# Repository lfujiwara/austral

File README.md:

# Austral

[Conheça a Austral](https://lfujiwara.github.io/austral/)

A Austral é uma plataforma de IoT AI-native para a cadeia de frio. Combina temperatura e consumo de energia de freezers e refrigeradores para ajudar mercados, bares e restaurantes a reduzir perdas de produtos e gastos com energia.

O dono recebe avisos pelo WhatsApp com a causa provável do problema e o valor do estoque em risco. Na mesma conversa, pode consultar o equipamento e chamar uma empresa de manutenção.

O técnico recebe um laudo com gráficos, modelo do equipamento e histórico de reparos. Empresas parceiras acompanham os chamados pelo webapp ou integram seus sistemas pelas APIs da Austral.

Projeto para a trilha Logística & automação do Hack Brasil 2026.

O firmware do dispositivo e o ambiente de desenvolvimento ficam em [`device/`](device/README.md).

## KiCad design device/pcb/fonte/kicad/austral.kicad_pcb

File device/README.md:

# Dispositivo

Firmware do dispositivo Austral e um ambiente de desenvolvimento virtual. O ambiente roda o firmware num ESP32 emulado, com sensores e Wi-Fi simulados, e mostra as leituras num gráfico. Não precisa de placa nem de sensores.

Esta branch é a variante offline. A buzina e a tela ficam fora do firmware que a placa roda. As seções "Buzina" e "Tela" explicam como religar.

## O que tem aqui

- `firmware/device.yaml`: firmware em ESPHome para ESP32.
- `firmware/packages/buzzer.yaml`: buzina no GPIO25 e as ações que a ligam no alarme local. A variante offline inclui `packages/buzzer_off.yaml` no lugar dele.
- `firmware/packages/buzzer_off.yaml`: pacote vazio incluído no lugar da buzina.
- `firmware/packages/display.yaml`: tela OLED. A variante offline inclui `packages/display_off.yaml` no lugar dele.
- `firmware/packages/display_off.yaml`: pacote vazio incluído no lugar da tela.
- `schema/mqtt.json`: formato de cada tópico MQTT que o dispositivo publica ou aceita.
- `emulator/`: script que compila o QEMU com Wi-Fi para ESP32 e os patches deste repositório.
- `server/`: servidor local. É o broker MQTT com TLS, serve a página com o gráfico e grava o histórico das leituras em `.local/data/`.
- `scenarios/`: roteiros que mudam a temperatura e o Wi-Fi ao longo do tempo.
- `test/e2e.mjs`: teste de ponta a ponta no emulador.
- `dev`: comando que reúne tudo. `./dev lan` prepara o broker TLS na rede de casa.

## Firmware

O firmware lê um DS18B20 no barramento 1-Wire do GPIO4, a sonda de ar. Ele pega o primeiro dispositivo que a busca ROM encontra no setup (`index: 0`), sem endereço gravado. Lê a cada 10 segundos, com resolução de 12 bits. O intervalo vai de 1 a 300 segundos e fica salvo na flash.

## Sensores e ligação

O DS18B20 da sonda de ar fica no barramento 1-Wire do GPIO4.

O HC-SR04 mede a distância até a porta. O Trig fica no GPIO26 e o Echo no GPIO27, atrás de um divisor de 1 kΩ e 2 kΩ. O sensor mede a cada 100 ms. O dispositivo publica a cada 500 ms a mediana das últimas 10 leituras, em metros. Sem eco, o valor é `nan`. "Door open" continua saindo dessa distância, depois da calibração.

O contato de porta é um reed switch MC-38, normalmente aberto, sem polaridade. Um fio vai no GPIO33 e o outro no GND. O ímã fica na porta. O pino usa o pull-up interno. Com o ímã perto, o contato fecha, o pino vai a nível baixo e a porta conta como fechada (`OFF`). Com o contato aberto, o pino fica em nível alto e a porta conta como aberta (`ON`). O estado sai em `binary_sensor/door_contact/state`, com um filtro de 100 ms. O emulador não simula esse pino: lá o valor não acompanha uma porta de verdade.

Para calibrar a distância, feche a porta e aperte "Calibrate door" na página web do dispositivo, ou publique `PRESS` em `button/calibrate_door/command`. O dispositivo mede por 3 segundos, calcula a mediana das leituras válidas e grava "Door closed distance". Com menos de 5 leituras válidas, mantém o valor antigo e registra um aviso no log. Esse valor também aceita ajuste manual e fica salvo na flash. O valor 0 significa sem calibração.

"Door open" fica `ON` quando a distância passa de "Door closed distance" mais 0,05 m por 2 segundos. Um eco ausente conta como porta aberta. Volta a `OFF` depois de 1 segundo. O estado da porta só é publicado depois da calibração. A margem é a substituição `door_margin` em `firmware/device.yaml`.

As leituras saem por MQTT com TLS na porta 8883. A seção "Formato dos dados" descreve os tópicos.

O alarme local observa a sonda de ar. O limite padrão é 5,0 °C. A entidade "Alarm threshold" guarda esse limite na flash. Dá para mudar pela página web do dispositivo ou por `number/alarm_threshold/command`, de -40 a 40 °C, em passos de 0,1. O alarme publica `ON` quando o ar fica acima do limite por 10 minutos e `OFF` 1 minuto depois de voltar ao limite ou abaixo. Funciona sem Wi-Fi e sem MQTT. Nesta variante o alarme local só publica o estado.

Nesta variante a tela não entra no firmware. O endereço do broker pode mudar pelo servidor web do dispositivo ou por MQTT. O novo endereço fica salvo na flash.

Para gravar numa placa real na rede de casa, siga a seção "Rede de casa no Mac". O código ROM da sonda aparece no log do primeiro boot.

## Buzina

O código da buzina continua no repositório, em `firmware/packages/buzzer.yaml`. Ele define a saída no GPIO25, a chave "Buzzer" e as ações que ligam e desligam essa chave quando o alarme local muda.

`firmware/device.yaml` escolhe o pacote pela substituição `buzzer_package`. A variante offline aponta para `packages/buzzer_off.yaml`. Esse pacote entra vazio: o GPIO25 fica livre e o alarme local fica só no MQTT.

Para reativar a buzina, troque a substituição e grave o firmware de novo:

```yaml
buzzer_package: packages/buzzer.yaml
```

A chave volta a publicar `switch/buzzer/state` (`ON` ou `OFF`) e a aceitar `switch/buzzer/command` (`ON`, `OFF` ou `TOGGLE`). Inclua esses dois tópicos de novo em `schema/mqtt.json` para o servidor e o `./dev test` aceitarem as mensagens. O teste também recusa qualquer tópico com `buzzer` no nome. Tire essa checagem ao religar a buzina.

## Tela

O código da tela continua no repositório, em `firmware/packages/display.yaml`. Ele liga o OLED SSD1306 de 128x32 no I2C, SDA no GPIO21 e SCL no GPIO22, endereço 0x3C. A tela alterna duas páginas a cada 6 segundos: o gráfico do ar nos últimos 30 minutos, com o valor atual e o limite ao lado, e a página com porta, alarme, Wi-Fi e MQTT.

`firmware/device.yaml` escolhe o pacote pela substituição `display_package`. Esta branch aponta para `packages/display_off.yaml`. Esse pacote entra vazio. O I2C não sobe e a tela não é inicializada.

Para religar a tela, troque a substituição e grave o firmware de novo:

```yaml
display_package: packages/display.yaml
```

## Formato dos dados

O arquivo `schema/mqtt.json` é a referência. Ele lista cada tópico com o padrão do payload, a unidade e a frequência. O servidor confere cada mensagem com esse arquivo. O teste falha se chegar um tópico fora dele ou um payload fora do padrão.

Os tópicos do dispositivo começam com `austral/<dispositivo>/`. O payload é texto puro, sem JSON. Essas mensagens saem com QoS 0 e `retain`. Quem assina recebe na hora o último valor de cada tópico.

| Tópico | Payload | Unidade | Frequência |
| --- | --- | --- | --- |
| `status` | `online` ou `offline` | | na conexão e na queda |
| `sensor/air_temperature/state` | número com uma casa, ou `nan` | °C | 10 s |
| `sensor/door_distance/state` | número com três casas, ou `nan` | m | 0,5 s |
| `sensor/wifi_signal/state` | inteiro | dBm | 60 s |
| `sensor/uptime/state` | inteiro | s | 60 s |
| `binary_sensor/door_contact/state` | `ON` ou `OFF` | | quando muda |
| `binary_sensor/door_open/state` | `ON` ou `OFF` | | quando muda, depois da calibração |
| `binary_sensor/local_temperature_alarm/state` | `ON` ou `OFF` | | quando muda |
| `text/mqtt_broker/state` | endereço do broker | | quando muda |
| `number/read_interval/state` | número | s | quando muda |
| `number/door_closed_distance/state` | número | m | quando muda |
| `number/alarm_threshold/state` | número | °C | quando muda |
| `debug` | linha de log do dispositivo | | a cada log |

Quando o checksum da sonda falha, o log `debug` traz um aviso `Scratch pad: 50.05.4B.46.7F.FF.0C.10.1C (1C)`. São os 9 bytes que a sonda enviou e, entre parênteses, o CRC que o firmware calculou com os 8 primeiros. O painel mostra essas linhas na seção Debug da sonda. O firmware usa uma cópia local do componente `dallas_temp` do ESPHome 2026.6.5 em `firmware/components/dallas_temp`. Ela difere do original em duas linhas: o nível do log do scratch pad inválido passa de DEBUG para WARN, e o setup registra o endereço encontrado pela busca (ou que nenhum dispositivo apareceu).

`nan` indica um sensor que não respondeu. O broker publica `offline` em nome do dispositivo quando perde a conexão com ele. `binary_sensor/door_open/state` só aparece depois da calibração.

O ESPHome também publica `esphome/discover/<dispositivo>` a cada conexão, com `retain`. O payload é um JSON com os endereços IP, o MAC, a versão do ESPHome e a placa. Esse tópico fica fora do prefixo e o servidor não confere o formato dele.

O dispositivo aceita cinco comandos: `text/mqtt_broker/command` (novo endereço), `number/read_interval/command` (segundos), `number/door_closed_distance/command` (metros), `number/alarm_threshold/command` (°C, de -40 a 40) e `button/calibrate_door/command` (`PRESS`).

A página do servidor mostra o último payload bruto de cada tópico e se ele bate com o schema.

## Histórico das leituras

O servidor grava cada leitura numérica num arquivo neste Mac, em `.local/data/readings-YYYY-MM-DD.jsonl`. A data do arquivo segue o fuso America/Sao_Paulo. A pasta `.local/` fica fora do git. Entram todos os sensores numéricos, por exemplo a temperatura do ar, a distância da porta, o sinal do Wi-Fi e o tempo ligado. Cada linha é um JSON:

```json
{"t":"2026-11-28T04:30:00.123-03:00","ms":1764315000123,"device":"austral-device","sensor":"air_temperature","value":22.8}
```

`t` é o instante com o fuso de Brasília. `value` é o número, ou `null` quando o sensor não respondeu (`nan`). O arquivo acumula o dia inteiro, sem o limite do gráfico. O painel continua usando um buffer em memória das últimas 4.320 leituras de cada sensor. Ao subir, o servidor recarrega do arquivo do dia as últimas 4.320 de cada um, para o gráfico não nascer vazio.

## Rede de casa no Mac

A placa manda as leituras para o broker MQTT deste repositório, com TLS e senha. O modo normal continua só em `127.0.0.1`. A rede de casa entra com `--lan` ou com `AUSTRAL_LAN=1`. Nesse modo a porta 8883 abre na rede, só com TLS. O gráfico fica em `http://127.0.0.1:8080`, neste Mac. Nenhuma porta sem TLS fica na rede.

A placa precisa do Wi-Fi de 2,4 GHz, o mesmo do Mac. Se o Mac estiver em `192.168.0.x`, o comando usa esse endereço. Se o IP mudar, rode `./dev lan prepare` de novo e grave o firmware outra vez. Rodar de novo mantém o mesmo usuário e a mesma senha.

Requisitos: Node 20.11 ou mais novo, Python 3 e `openssl`. O `openssl` já vem no macOS. Não precisa de Docker.

```sh
cd device
./dev lan prepare
```

O comando grava em `firmware/secrets.yaml`, sem mostrar senha:

- `mqtt_broker`: o IP da rede, por exemplo `192.168.0.23`. Use esse IP. O certificado também traz o nome `<hostname>.local`. Só troque `mqtt_broker` por esse nome se quiser que a placa disque o nome em vez do IP.
- `mqtt_username` e `mqtt_password`: gerados em `.local/credentials.env`.
- `mqtt_ca`: o conteúdo de `.local/tls/ca.pem`, a autoridade que assina o broker. O comando cola esse texto no secrets. Não use o certificado do servidor no lugar da autoridade.

`wifi_ssid` e `wifi_password` não são alterados. Se ainda estiverem de exemplo, preencha os dois no mesmo arquivo. Não copie o arquivo para outro lugar.

Grave a placa, ligada por USB:

```sh
cd device
python3 -m venv .local/venv
.local/venv/bin/pip install 'esphome==2026.9.1'
cd firmware
../.local/venv/bin/esphome run device.yaml
```

Suba o broker. O gráfico abre só neste Mac.

```sh
cd device
./dev server --lan
```

Para subir também o ESP32 emulado, use `./dev up --lan` ou `AUSTRAL_LAN=1 ./dev up`. Sem `--lan` e sem a variável, tudo continua em `127.0.0.1`.

Se o firewall do macOS estiver ligado, ele pode perguntar se o Node pode aceitar conexões de entrada. Permita. Se a pergunta não aparecer: Ajustes do Sistema, Rede, Firewall, Opções, e permita o Node. A única porta na rede é a 8883, com TLS e senha.

## Senha de atualização pelo Wi-Fi (OTA)

A senha de atualização OTA gravada na placa desde 28/11/2026 é `23): E86CtanNULRABrIz`.

Se a gravação pelo Wi-Fi conectar e depois falhar com `Failed to upload`, a senha que está na placa é diferente da que está no `secrets.yaml`. Foi o que aconteceu em 28/11/2026. Nesse caso, grave pelo USB (desligue a bateria antes):

```sh
cd device/firmware
~/austral-tools/venv/bin/esphome run device.yaml --device /dev/cu.usbserial-5C3E0313501
```

## Ambiente virtual

Requisitos: macOS com Homebrew, Node 20.11 ou mais novo, `uv`, `git`, `openssl` e acesso à internet. O setup baixa o QEMU, o ESPHome e as ferramentas de compilação do ESP32.

```sh
cd device
./dev setup   # compila o emulador, instala o ESPHome e o servidor
./dev build   # compila o firmware para o emulador
./dev up      # sobe o servidor e o ESP32 emulado
```

O gráfico abre em http://127.0.0.1:8080. O servidor web do dispositivo emulado abre em http://127.0.0.1:18080. O log serial fica em `.local/run/device.log`. Para parar, rode `./dev down`.

Com o ambiente no ar, a sonda e o Wi-Fi mudam assim:

```sh
./dev temps -21.25        # ar em °C
./dev temps unplugged     # a sonda de ar sai do barramento
./dev wifi off            # o ponto de acesso cai
./dev wifi on
./dev scenario warm-up    # o ar passa de 5 °C e o alarme local muda; a buzina continua desligada
```

Os cenários prontos são `warm-up`, `sensor-unplug` e `wifi-drop`.

Para testar uma mudança no firmware, edite `firmware/device.yaml` e rode `./dev ota` com o ambiente no ar. O comando compila e envia o firmware por OTA, como numa placa real. O dispositivo reinicia na versão nova sem perder a flash. `./dev build` grava uma flash nova e só roda com o dispositivo parado.

`./dev test` sobe tudo e confere a conexão, a hora por SNTP, as leituras, a sonda desconectada, a volta depois de uma queda do Wi-Fi, uma atualização por OTA, o schema de todas as mensagens, o limite padrão de 5 °C e a ausência da buzina.

## Como o emulador funciona

O QEMU vem do fork [lcgamboa/qemu](https://github.com/lcgamboa/qemu), no commit `64aed503e3`. Esse fork emula o rádio Wi-Fi do ESP32. O emulador cria três redes abertas: `PICSimLabWifi`, `Espressif` e `MasseyWifi`. O firmware do ambiente virtual usa a `PICSimLabWifi`.

Os patches em `emulator/patches` acrescentam duas coisas:

- Sensores DS18B20 no 1-Wire. O modelo lê os pulsos do firmware e responde como os sensores. As temperaturas vêm de `.local/control/temperatures.txt`.
- Um interruptor do Wi-Fi. Com `off` em `.local/control/wifi.txt`, as redes somem e o dispositivo é desconectado.

O QEMU roda com `-icount`. Sem isso, o 1-Wire perde a sincronia.

O build do ambiente virtual inclui `device.yaml` e muda só o nível de log para DEBUG. O firmware é o mesmo da placa.

O servidor e o emulador escutam só em `127.0.0.1`. Certificados, senhas, o firmware compilado e o histórico das leituras ficam em `.local/`, fora do git.

## Licenças

O QEMU e os patches em `emulator/patches` seguem a GPL-2.0. O restante deste diretório segue a licença MIT do repositório.

## Limites

O ambiente virtual não emula o display OLED nem o HC-SR04. No emulador, `door_distance` fica em `nan` e a calibração falha por falta de leituras. `binary_sensor/door_open` não é publicado. O emulador também não simula o reed switch no GPIO33. `door_contact` não segue a abertura de uma porta. O sinal do Wi-Fi é sorteado pelo emulador e não reflete distância nem obstáculos. As redes virtuais não têm senha. Ruído elétrico e falhas de alimentação não são simulados. Algumas leituras falham no 1-Wire emulado e chegam como `nan`, com mais frequência logo depois do boot.

## Próximos passos

- P1: simular ruído elétrico nos sensores.
- P2: simular o display OLED.
- P3: variar o sinal do Wi-Fi e usar redes com senha.

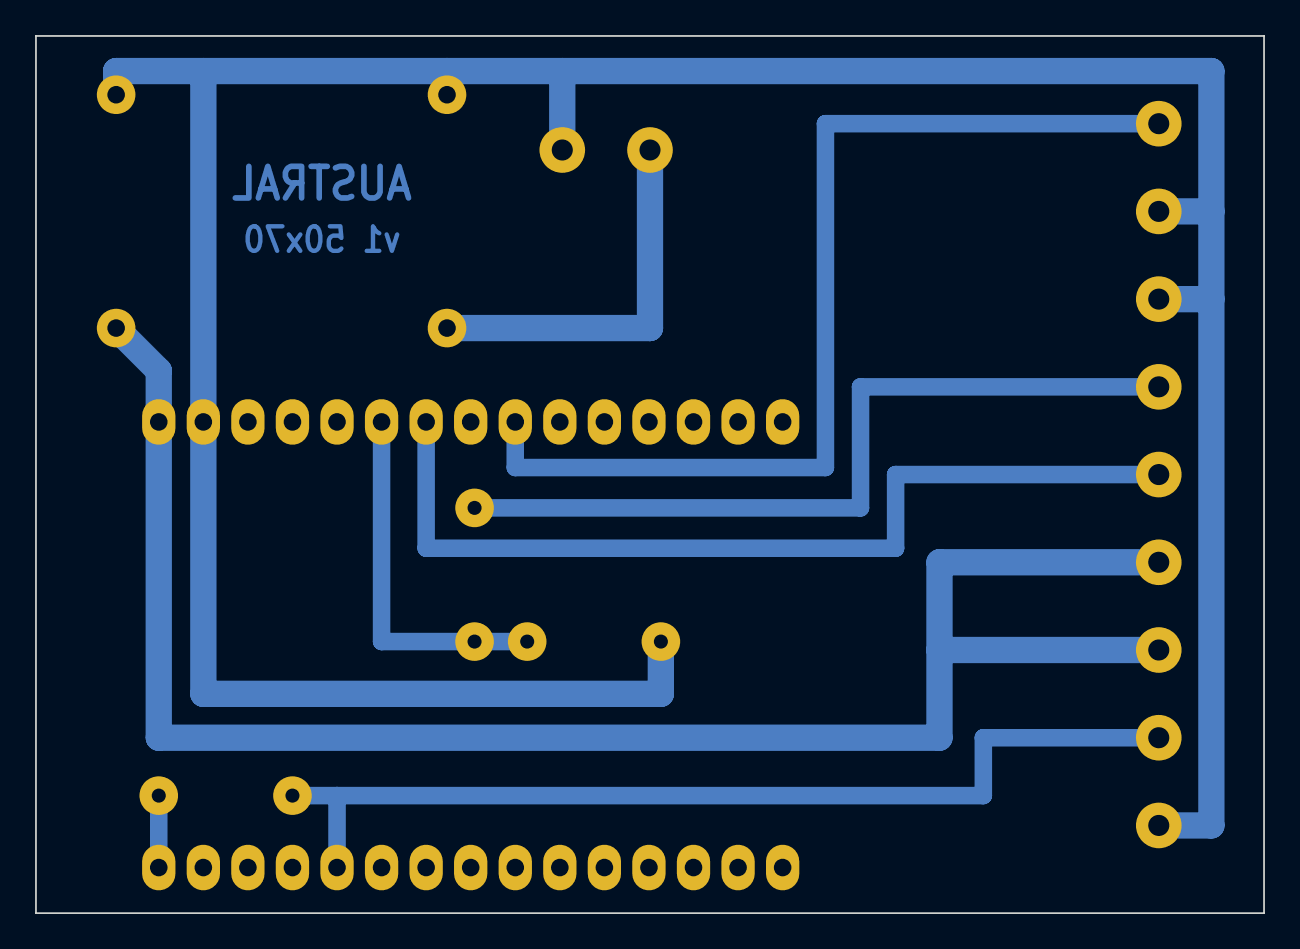
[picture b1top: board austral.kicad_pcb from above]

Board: 2 copper layers, 70.0 x 50.0 mm, 9 parts (0 on the bottom side), 9 nets.

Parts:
J1: BAT 2S (do BMS)
J2: DS18B20
J3: HC-SR04
J4: REED MC-38
R1: 4,7 kΩ
R2: 1 kΩ
R3: 2 kΩ
U1: ESP32 DevKit V1 (DOIT 30p)
U2: MP1584EN

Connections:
+3V3: R1.1, U1.30
+5V: J2.1, J3.1, U1.15, U2.OUT+
DQ: J2.2, R1.2, U1.26
ECHO: R2.2, R3.1, U1.10
ECHO5V: J3.3, R2.1
GND: J1.1, J2.3, J3.4, J4.2, R3.2, U1.14, U2.IN-, U2.OUT-
REED: J4.1, U1.7
TRIG: J3.2, U1.9
VBAT: J1.2, U2.IN+

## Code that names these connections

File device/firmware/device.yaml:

substitutions:
  device_name: austral-device
  # Meters above the closed-door baseline before the door counts as open.
  door_margin: "0.05"
  # Offline variant. Set this to packages/buzzer.yaml to enable the audible alarm.
  buzzer_package: packages/buzzer_off.yaml
  # Offline variant. Set this to packages/display.yaml to enable the OLED.
  display_package: packages/display_off.yaml
  default_broker: !secret mqtt_broker

packages:
  buzzer: !include ${buzzer_package}
  display: !include ${display_package}

esphome:
  name: ${device_name}
  friendly_name: Austral Device
  on_boot:
    priority: -100
    then:
      - lambda: |-
          float interval = id(read_interval).state;
          if (std::isnan(interval) || interval < 1 || interval > 300) {
            ESP_LOGW("read_interval", "Restored read interval %g s is invalid, using 10 s", interval);
            id(read_interval).make_call().set_value(10).perform();
          } else {
            id(air_temperature)->stop_poller();
            id(air_temperature)->set_update_interval((uint32_t) interval * 1000);
            id(air_temperature)->start_poller();
          }
          if (id(mqtt_broker).state.size() >= 3 && id(mqtt_broker).state != "${default_broker}") {
            id(mqtt_client)->set_broker_address(id(mqtt_broker).state);
            id(mqtt_client)->disable();
            id(mqtt_client)->enable();
          }
      # Setup runs before the web server accepts /events. Repeat the search result once the device is on the network.
      - delay: 10s
      - lambda: id(air_temperature)->log_search_result();

esp32:
  board: esp32dev

# Local copy of the ESPHome dallas_temp component. It differs from upstream in two places: the scratch pad
# bytes of a failed checksum are logged at WARN instead of DEBUG, and setup logs the ROM found by the
# One-Wire search (or that none was found) at WARN/INFO so it appears at the INFO log level. See
# components/dallas_temp/dallas_temp.cpp.
external_components:
  - source:
      type: local
      path: components
    components: [dallas_temp]

logger:
  level: INFO
  logs:
    # A missing echo is expected and published as nan. Do not log it ten times a second.
    ultrasonic.sensor: ERROR

wifi:
  id: wifi_client
  ssid: !secret wifi_ssid
  password: !secret wifi_password
  # Lower peak transmit current for boards with a weak 3.3 V regulator.
  output_power: 8.5dB
  ap:
    ssid: "Austral-Device-Fallback"
    password: !secret fallback_password

captive_portal:

web_server:
  port: 80

ota:
  - platform: esphome
    password: !secret ota_password

time:
  - platform: sntp
    id: sntp_time

mqtt:
  id: mqtt_client
  broker: !secret mqtt_broker
  port: 8883
  certificate_authority: !secret mqtt_ca
  username: !secret mqtt_username
  password: !secret mqtt_password
  topic_prefix: austral/${device_name}
  discovery: false

one_wire:
  - platform: gpio
    pin: GPIO4
    id: one_wire_bus

sensor:
  - platform: dallas_temp
    one_wire_id: one_wire_bus
    # First device found by the GPIO4 One-Wire ROM search at setup. No stored ROM address.
    index: 0
    name: "Air temperature"
    id: air_temperature
    resolution: 12
    update_interval: 10s

  - platform: wifi_signal
    name: "WiFi signal"
    update_interval: 60s

  - platform: uptime
    name: "Uptime"
    update_interval: 60s

  # HC-SR04: Trig on GPIO26, Echo on GPIO27 through a 1k/2k divider.
  # Raw reads every 100 ms feed the calibration. Published every 500 ms as the median of the last 10 reads.
  - platform: ultrasonic
    trigger_pin: GPIO26
    echo_pin: GPIO27
    name: "Door distance"
    id: door_distance
    update_interval: 100ms
    accuracy_decimals: 3
    filters:
      - median:
          window_size: 10
          send_every: 5
    on_raw_value:
      - lambda: |-
          if (id(calibrating) && !std::isnan(x) && x > 0) id(calibration_samples).push_back(x);

globals:
  - id: calibrating
    type: bool
    initial_value: "false"
  - id: calibration_samples
    type: std::vector<float>

script:
  - id: calibrate_door
    mode: single
    then:
      - lambda: |-
          id(calibration_samples).clear();
          id(calibrating) = true;
      - delay: 3s
      - lambda: |-
          id(calibrating) = false;
          auto &samples = id(calibration_samples);
          if (samples.size() < 5) {
            ESP_LOGW("calibrate", "Door calibration failed: %u valid samples, need 5. Baseline unchanged.", (unsigned) samples.size());
            return;
          }
          std::sort(samples.begin(), samples.end());
          float median = samples.size() % 2 ? samples[samples.size() / 2] : (samples[samples.size() / 2 - 1] + samples[samples.size() / 2]) / 2;
          ESP_LOGI("calibrate", "Door closed distance %.3f m from %u samples", median, (unsigned) samples.size());
          id(door_closed_distance).make_call().set_value(median).perform();
          samples.clear();

button:
  - platform: template
    name: "Calibrate door"
    id: calibrate_door_button
    on_press:
      - script.execute: calibrate_door

text:
  - platform: template
    name: "MQTT broker"
    id: mqtt_broker
    mode: text
    optimistic: true
    min_length: 3
    max_length: 64
    initial_value: !secret mqtt_broker
    restore_value: true
    set_action:
      - lambda: |-
          id(mqtt_client)->set_broker_address(x);
          id(mqtt_client)->disable();
          id(mqtt_client)->enable();

number:
  - platform: template
    name: "Read interval"
    id: read_interval
    unit_of_measurement: s
    min_value: 1
    max_value: 300
    step: 5
    initial_value: 10
    restore_value: true
    optimistic: true
    set_action:
      - lambda: |-
          id(air_temperature)->stop_poller();
          id(air_temperature)->set_update_interval((uint32_t) x * 1000);
          id(air_temperature)->start_poller();

  - platform: template
    name: "Door closed distance"
    id: door_closed_distance
    unit_of_measurement: m
    min_value: 0
    max_value: 4
    step: 0.001
    mode: box
    initial_value: 0
    restore_value: true
    optimistic: true

  - platform: template
    name: "Alarm threshold"
    id: alarm_threshold
    unit_of_measurement: "°C"
    min_value: -40
    max_value: 40
    step: 0.1
    mode: box
    initial_value: 5.0
    restore_value: true
    optimistic: true

binary_sensor:
  # MC-38 reed, normally open, one wire on GPIO33 and the other on GND.
  # Internal pull-up: contact closed (magnet near) pulls the pin low and the door is shut.
  # Contact open leaves the pin high and the door is open. device_class door uses ON for open.
  - platform: gpio
    name: "Door contact"
    id: door_contact
    device_class: door
    pin:
      number: GPIO33
      mode:
        input: true
        pullup: true
      inverted: false
    filters:
      - delayed_on: 100ms
      - delayed_off: 100ms

  - platform: template
    name: "Door open"
    id: door_open
    device_class: door
    lambda: |-
      float closed = id(door_closed_distance).state;
      if (std::isnan(closed) || closed <= 0 || !id(door_distance).has_state()) return {};
      float distance = id(door_distance).state;
      return std::isnan(distance) || distance > closed + ${door_margin};
    filters:
      - delayed_on: 2s
      - delayed_off: 1s

  - platform: template
    name: "Local temperature alarm"
    id: local_alarm
    lambda: |-
      float threshold = id(alarm_threshold).state;
      if (!id(air_temperature).has_state() || std::isnan(threshold)) return {};
      return id(air_temperature).state > threshold;
    filters:
      - delayed_on: 10min
      - delayed_off: 1min
